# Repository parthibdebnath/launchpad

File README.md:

# launchpad
10-key Macropad with custom PCB, case, and firmware! Two Neopixel LEDs are part of the PCB as well as a XIAO RP2040 MCU. Can be used as a numpad, function keys, or custom actions. PCB designed in KiCad, case in Fusion and Blender, and KMK firmware.

Current functionality looks like this(the keys are in a 3x3 grid with a centered bottom key):

PREV SONG // NEXT SONG // PLAY-PAUSE <br>
VOL UP    // VOL DOWN  // MUTE <br>
REWIND    // FAST FWD  // FILES <br>
          // LOCK PC   // <br>

**Finished product 3D model (Blender):**  

**Case (Fusion):**  

**PCB (KiCad):**  

**Schematic (KiCad):**  

**BOM:**
- 1× Seeed XIAO RP2040  
- 10× Cherry MX Switches  
- 10× Blank DSA Keycaps (White)  
- 2× SK6812 MINI-E LEDs  
- 4× M3×5mm×4mm heatset inserts  
- 4× M3×16mm screws

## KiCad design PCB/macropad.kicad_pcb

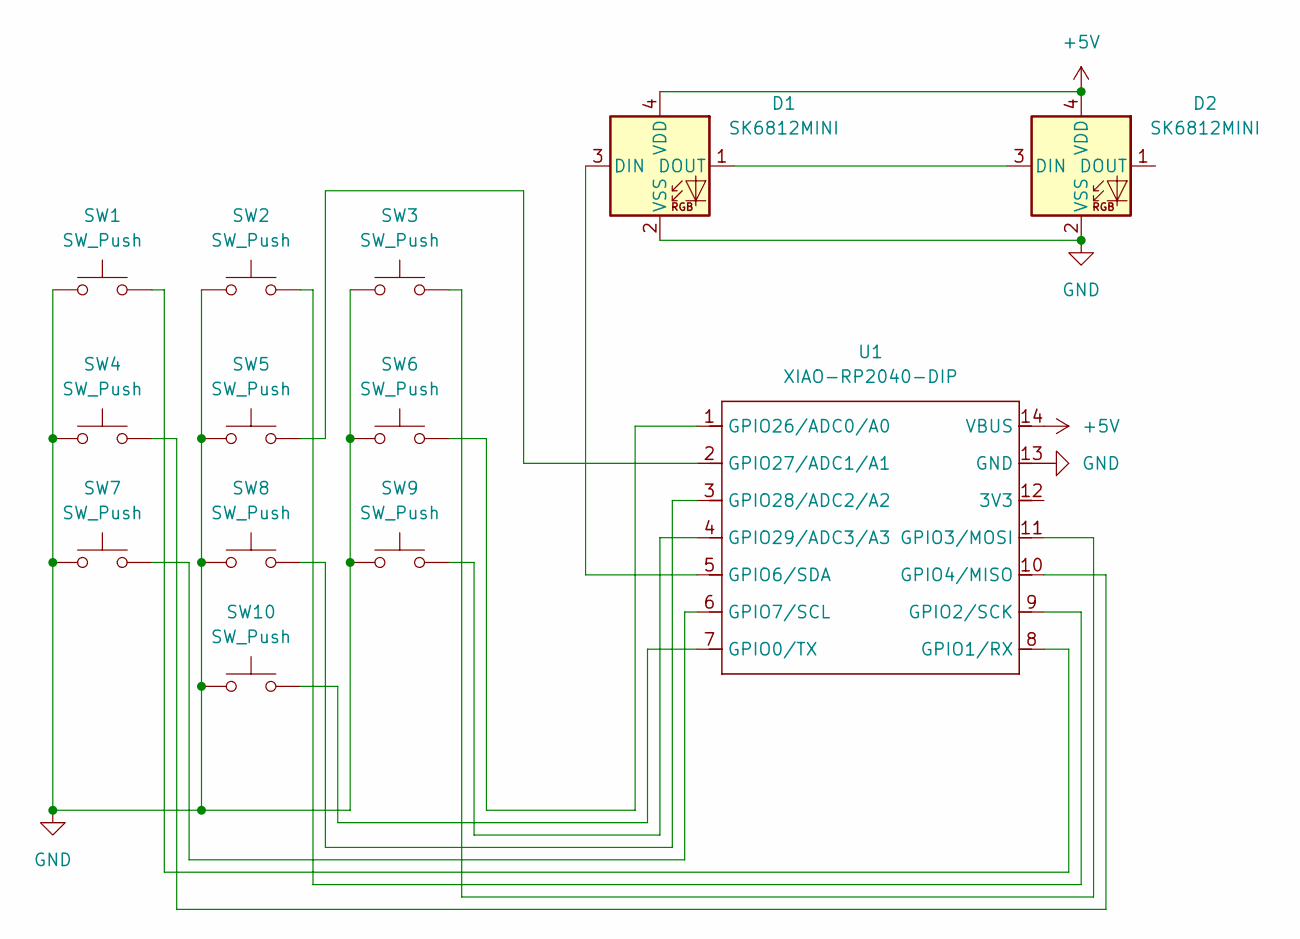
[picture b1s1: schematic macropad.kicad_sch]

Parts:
D1, D2: SK6812MINI; LED_SK6812MINI_PLCC4_3.5x3.5mm_P1.75mm
SW1, SW2, SW3, SW4, SW5, SW6, SW7, SW8, SW9, SW10: SW_Push; SW_Cherry_MX_1.00u_PCB
U1: XIAO-RP2040-DIP

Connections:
+5V: D1.4 (VDD), D2.4 (VDD), U1.14 (VBUS)
GND: D1.2 (VSS), D2.2 (VSS), SW1.1, SW2.1, SW3.1, SW4.1, SW5.1, SW6.1, SW7.1, SW8.1, SW9.1, SW10.1, U1.13 (GND)
unnamed: D1.3 (DIN), U1.5 (GPIO6/SDA)
unnamed: D1.1 (DOUT), D2.3 (DIN)
unnamed: SW10.2, U1.7 (GPIO0/TX)
unnamed: SW1.2, U1.8 (GPIO1/RX)
unnamed: SW2.2, U1.9 (GPIO2/SCK)
unnamed: SW3.2, U1.11 (GPIO3/MOSI)
unnamed: SW4.2, U1.10 (GPIO4/MISO)
unnamed: SW7.2, U1.6 (GPIO7/SCL)
unnamed: SW6.2, U1.1 (GPIO26/ADC0/A0)
unnamed: SW5.2, U1.2 (GPIO27/ADC1/A1)
unnamed: SW8.2, U1.3 (GPIO28/ADC2/A2)
unnamed: SW9.2, U1.4 (GPIO29/ADC3/A3)

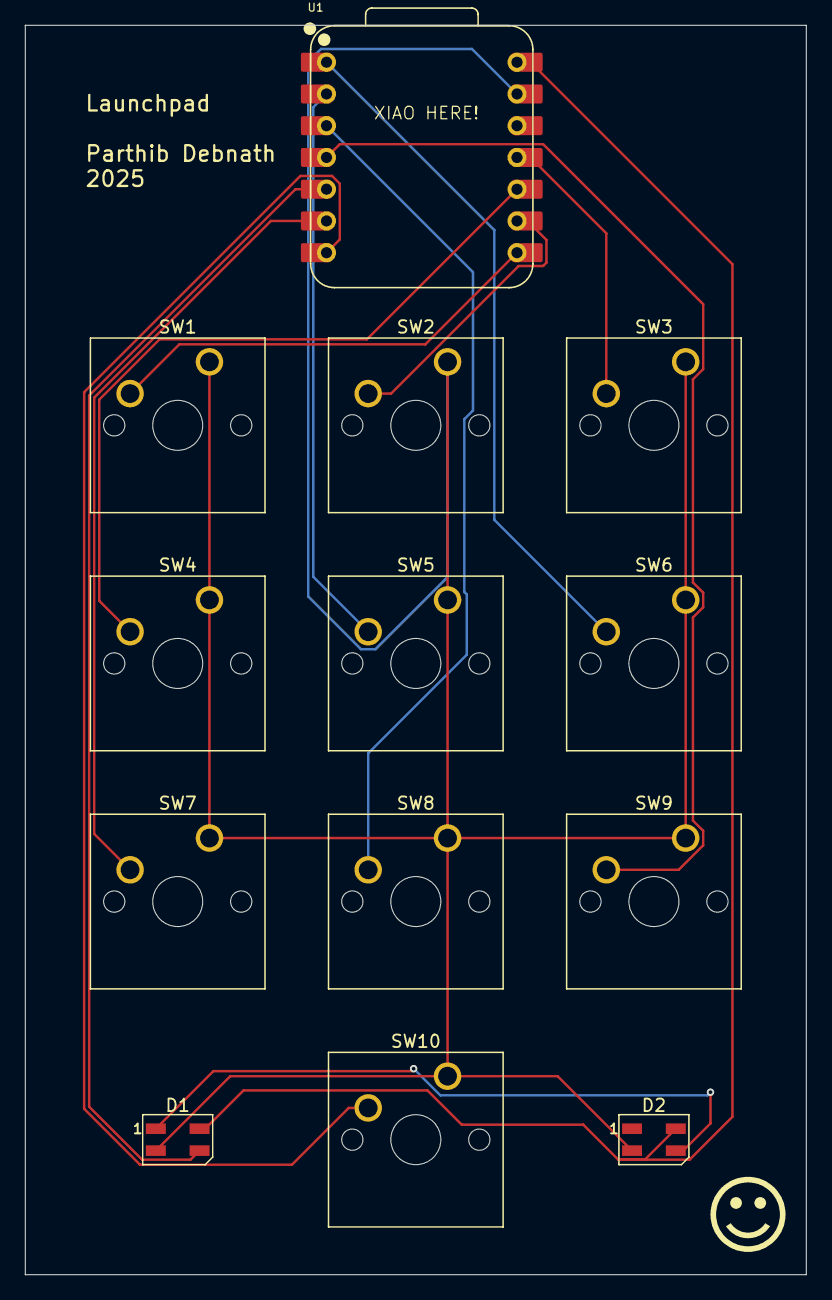
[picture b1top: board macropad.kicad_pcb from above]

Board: 2 copper layers, 62.5 x 100.0 mm, 13 parts (0 on the bottom side), 14 nets.
